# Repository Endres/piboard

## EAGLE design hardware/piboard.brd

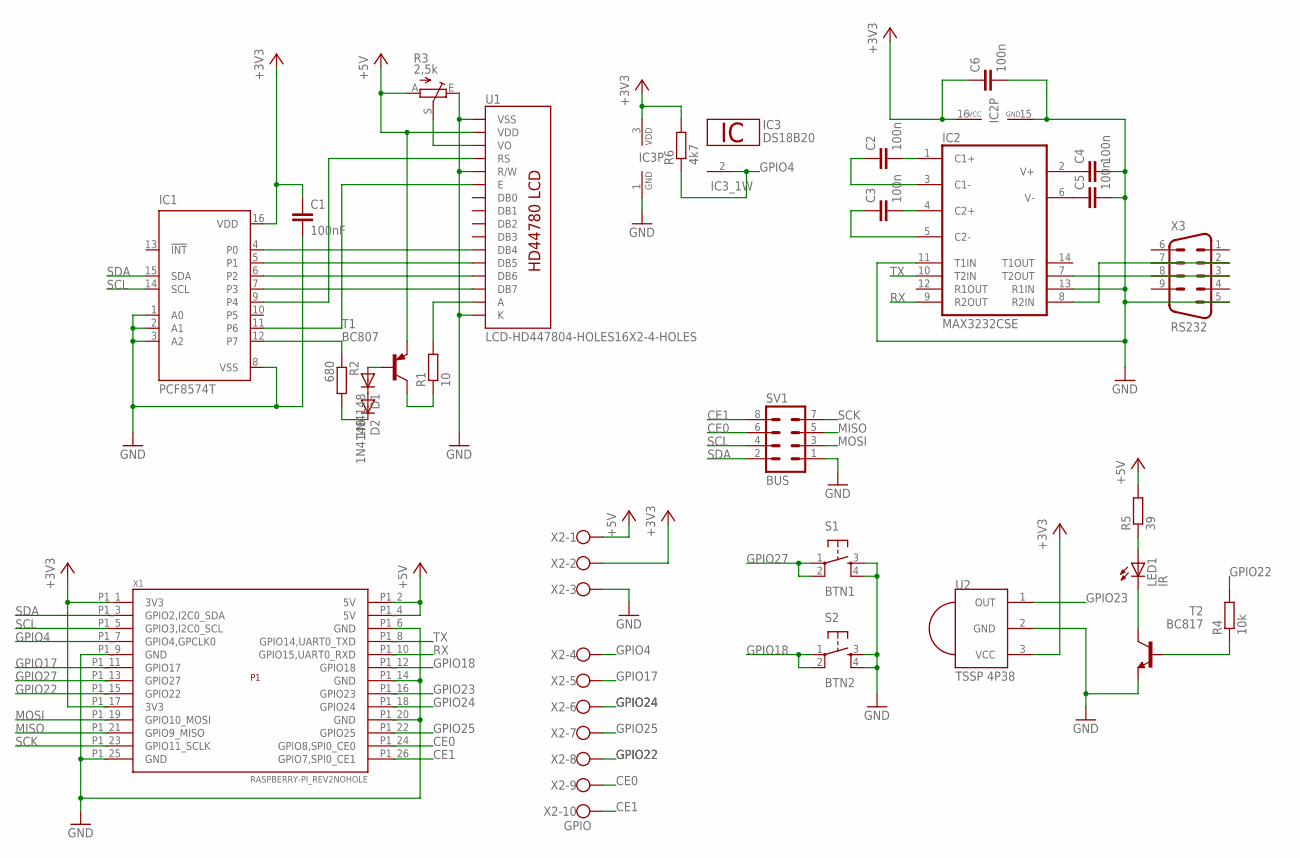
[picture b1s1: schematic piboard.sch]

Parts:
C1: 100nF; C0805
C2, C3, C4, C5, C6: 100n; C0805
D1, D2: 1N4148; SOD80C
IC1: PCF8574T; SO16W
IC2: MAX3232CSE; SO16
IC3: DS18B20; TO92-
LED1: IR; LED5MM
R1: 10; R0805
R2: 680; R0805
R3: 2,5k; LI6
R4: 10k; R0805
R5: 39; R0805
R6: 4k7; R0805
S1: BTN1; TACTILE-PTH
S2: BTN2; TACTILE-PTH
SV1: BUS; MA04-2
T1: BC807; SOT23-BEC
T2: BC817; SOT23-BEC
U1: LCD-HD447804-HOLES16X2-4-HOLES; LCD-16X2-4HOLES
U2: TSSP 4P38; PNA460XM
X1: RASPBERRY-PI_REV2NOHOLE; RASPBERRY-PI_REV2_NOHOLE
X2: GPIO; RIA059-10
X3: RS232; M09HP

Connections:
+3V3: C1.1, C6.1, IC1.16 (VDD), IC2.16 (VCC), IC3.3 (VDD), R6.2, U2.3 (VCC), X1.P1_1 (3V3), X1.P1_17 (3V3), X2.2
+5V: R3.A, R5.2, T1.E, U1.2 (VDD), X1.P1_2 (5V), X1.P1_4 (5V), X2.1
CE0: SV1.6, X1.P1_24 (GPIO8,SPI0_CE0), X2.9
CE1: SV1.8, X1.P1_26 (GPIO7,SPI0_CE1), X2.10
GND: C1.2, C4.2, C5.2, C6.2, IC1.1 (A0), IC1.2 (A1), IC1.3 (A2), IC1.8 (VSS), IC2.11 (T1IN), IC2.13 (R1IN), IC2.15 (GND), IC3.1 (GND), R3.E, S1.3, S1.4, S2.3, S2.4, SV1.1, T2.E, U1.1 (VSS), U1.5 (R/W), U1.16 (K), U2.2 (GND), X1.P1_6 (GND), X1.P1_9 (GND), X1.P1_14 (GND), X1.P1_20 (GND), X1.P1_25 (GND), X2.3, X3.5
GPIO4: IC3.2 (1W), R6.1, X1.P1_7 (GPIO4,GPCLK0), X2.4
GPIO17: X1.P1_11 (GPIO17), X2.5
GPIO18: S2.1, S2.2, X1.P1_12 (GPIO18)
GPIO22: R4.2, X1.P1_15 (GPIO22), X2.8
GPIO23: U2.1 (OUT), X1.P1_16 (GPIO23)
GPIO24: X1.P1_18 (GPIO24), X2.6
GPIO25: X1.P1_22 (GPIO25), X2.7
GPIO27: S1.1, S1.2, X1.P1_13 (GPIO27)
MISO: SV1.5, X1.P1_21 (GPIO9_MISO)
MOSI: SV1.3, X1.P1_19 (GPIO10_MOSI)
unnamed: R1.1, T1.C
unnamed: IC1.9 (P4), U1.4 (RS)
unnamed: IC1.4 (P0), U1.11 (DB4)
unnamed: IC1.5 (P1), U1.12 (DB5)
unnamed: IC1.6 (P2), U1.13 (DB6)
unnamed: IC1.7 (P3), U1.14 (DB7)
unnamed: IC1.11 (P6), U1.6 (E)
unnamed: R1.2, U1.15 (A)
unnamed: IC1.12 (P7), R2.1
unnamed: D1.A, T1.B
unnamed: D1.C, D2.A
unnamed: D2.C, R2.2
unnamed: R3.S, U1.3 (VO)
unnamed: C2.2, IC2.1 (C1+)
unnamed: C3.2, IC2.4 (C2+)
unnamed: C2.1, IC2.3 (C1-)
unnamed: C3.1, IC2.5 (C2-)
unnamed: IC2.7 (T2OUT), X3.3
unnamed: IC2.8 (R2IN), X3.2
unnamed: C4.1, IC2.2 (V+)
unnamed: C5.1, IC2.6 (V-)
unnamed: R4.1, T2.B
unnamed: LED1.A, R5.1
unnamed: LED1.K (C), T2.C
RX: IC2.9 (R2OUT), X1.P1_10 (GPIO15,UART0_RXD)
SCK: SV1.7, X1.P1_23 (GPIO11_SCLK)
SCL: IC1.14 (SCL), SV1.4, X1.P1_5 (GPIO3,I2C0_SCL)
SDA: IC1.15 (SDA), SV1.2, X1.P1_3 (GPIO2,I2C0_SDA)
TX: IC2.10 (T2IN), X1.P1_8 (GPIO14,UART0_TXD)

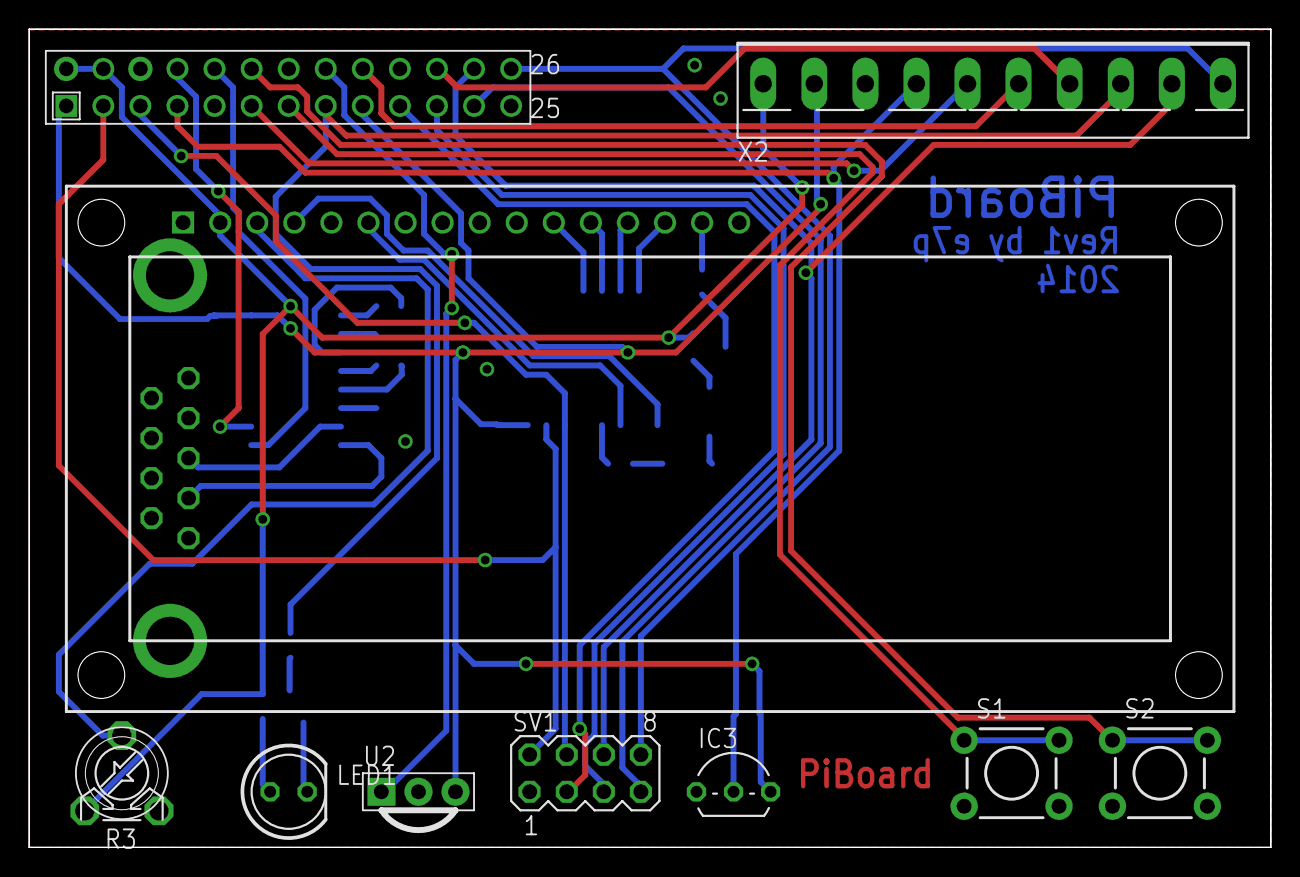
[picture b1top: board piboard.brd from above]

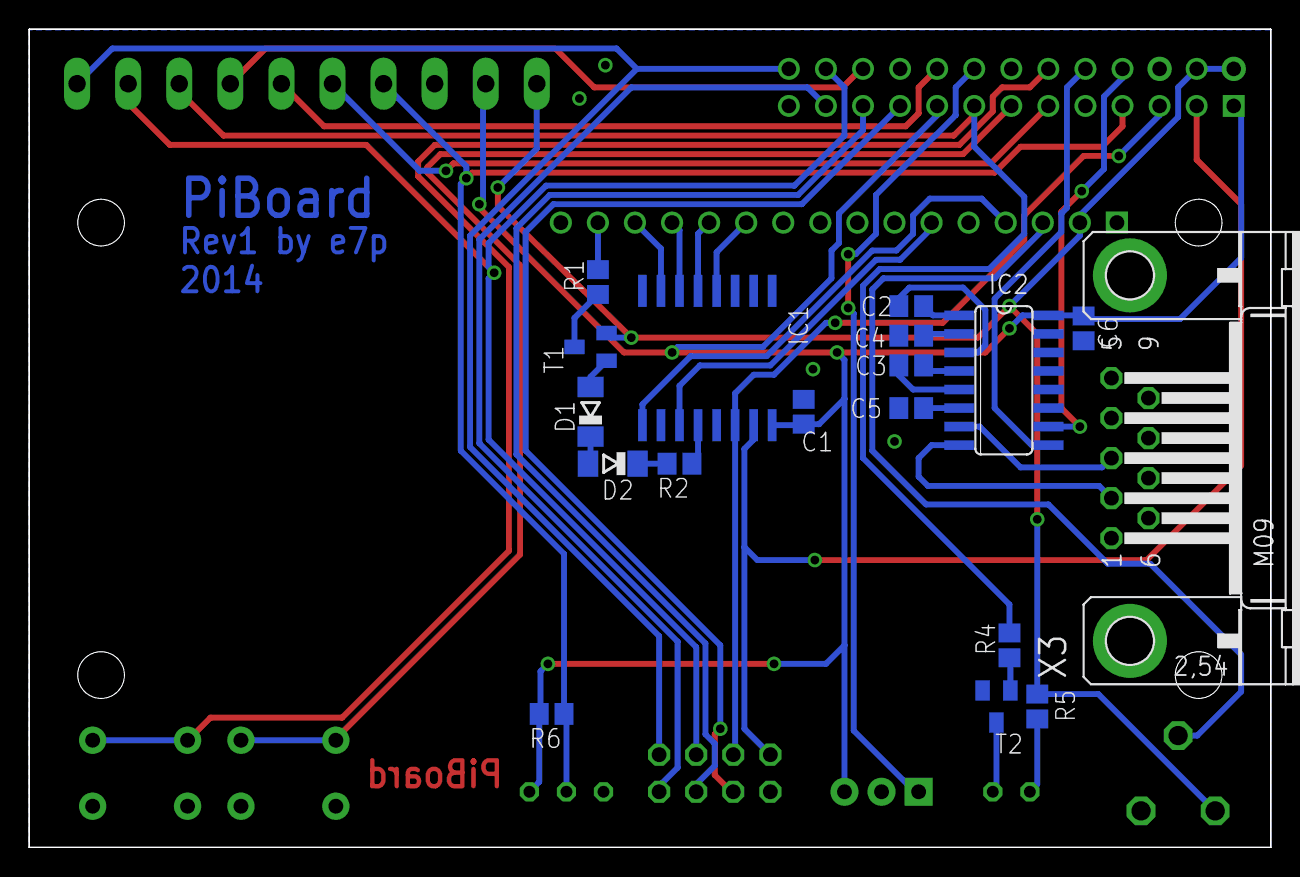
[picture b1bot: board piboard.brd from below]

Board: 2 copper layers, 85.1 x 56.1 mm, 28 parts (18 on the bottom side), 44 nets.

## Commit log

2014-09-26 initial commit containing an analog clock for the LCD display
2014-09-26 unified spacing
2014-09-26 Getting Menu to work. Buttons make still some problems
2014-09-26 Other Files related menu changes
2014-09-26 satisfied solution for the buttons in the menu
2014-09-26 current state of the menu
2014-10-24 hardware added

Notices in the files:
parts and their libraries:
SparkFun_eagle5: Licensing: CC v3.0 Share-Alike You are welcome to use this library for commercial purposes.
